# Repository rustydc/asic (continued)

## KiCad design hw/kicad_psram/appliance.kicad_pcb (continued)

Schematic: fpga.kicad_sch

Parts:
J_BMC_NET: BMC Ethernet; RJ45_MAGJACK
J_HOST: SlimSAS 8i host cable; SLIMSAS_8I
J_SFP: SFP+ cage; SFP_CAGE
U_BMC: BMC SoC; BGA_BMC_21x21
U_CLK: Si5345; QFN64_9x9
U_FPGA: XCAU15P-2FFVB676E; FFVB676_26x26_P1.0

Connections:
BMC_ETH0_N: J_BMC_NET.2, U_BMC.2
BMC_ETH0_P: J_BMC_NET.1, U_BMC.1
BMC_ETH1_N: J_BMC_NET.4, U_BMC.4
BMC_ETH1_P: J_BMC_NET.3, U_BMC.3
BMC_ETH2_N: J_BMC_NET.6, U_BMC.6
BMC_ETH2_P: J_BMC_NET.5, U_BMC.5
BMC_ETH3_N: J_BMC_NET.8, U_BMC.8
BMC_ETH3_P: J_BMC_NET.7, U_BMC.7
DDR4_ADDR_CMD0: U_FPGA.L24; also elsewhere on the board
DDR4_ADDR_CMD1: U_FPGA.M24; also elsewhere on the board
DDR4_ADDR_CMD2: U_FPGA.N24; also elsewhere on the board
DDR4_ADDR_CMD3: U_FPGA.P24; also elsewhere on the board
DDR4_ADDR_CMD4: U_FPGA.R24; also elsewhere on the board
DDR4_ADDR_CMD5: U_FPGA.T24; also elsewhere on the board
DDR4_ADDR_CMD6: U_FPGA.U24; also elsewhere on the board
DDR4_ADDR_CMD7: U_FPGA.V24; also elsewhere on the board
DDR4_ADDR_CMD8: U_FPGA.W24; also elsewhere on the board
DDR4_ADDR_CMD9: U_FPGA.Y24; also elsewhere on the board
DDR4_ADDR_CMD10: U_FPGA.AA24; also elsewhere on the board
DDR4_ADDR_CMD11: U_FPGA.AB24; also elsewhere on the board
DDR4_ADDR_CMD12: U_FPGA.C25; also elsewhere on the board
DDR4_ADDR_CMD13: U_FPGA.D25; also elsewhere on the board
DDR4_ADDR_CMD14: U_FPGA.E25; also elsewhere on the board
DDR4_ADDR_CMD15: U_FPGA.F25; also elsewhere on the board
DDR4_ADDR_CMD16: U_FPGA.G25; also elsewhere on the board
DDR4_ADDR_CMD17: U_FPGA.H25; also elsewhere on the board
DDR4_ADDR_CMD18: U_FPGA.J25; also elsewhere on the board
DDR4_ADDR_CMD19: U_FPGA.K25; also elsewhere on the board
DDR4_ADDR_CMD20: U_FPGA.L25; also elsewhere on the board
DDR4_ADDR_CMD21: U_FPGA.M25; also elsewhere on the board
DDR4_ADDR_CMD22: U_FPGA.N25; also elsewhere on the board
DDR4_ADDR_CMD23: U_FPGA.P25; also elsewhere on the board
DDR4_ADDR_CMD24: U_FPGA.R25; also elsewhere on the board
DDR4_ADDR_CMD25: U_FPGA.T25; also elsewhere on the board
DDR4_ADDR_CMD26: U_FPGA.U25; also elsewhere on the board
DDR4_ADDR_CMD27: U_FPGA.V25; also elsewhere on the board
DDR4_CK_N: U_FPGA.Y25; also elsewhere on the board
DDR4_CK_P: U_FPGA.W25; also elsewhere on the board
DDR4_CTRL0: U_FPGA.AA25; also elsewhere on the board
DDR4_CTRL1: U_FPGA.AB25; also elsewhere on the board
DDR4_CTRL2: U_FPGA.C26; also elsewhere on the board
DDR4_CTRL3: U_FPGA.D26; also elsewhere on the board
DDR4_CTRL4: U_FPGA.E26; also elsewhere on the board
DDR4_CTRL5: U_FPGA.F26; also elsewhere on the board
DDR4_DM0: U_FPGA.C24; also elsewhere on the board
DDR4_DM1: U_FPGA.D24; also elsewhere on the board
DDR4_DM2: U_FPGA.E24; also elsewhere on the board
DDR4_DM3: U_FPGA.F24; also elsewhere on the board
DDR4_DM4: U_FPGA.G24; also elsewhere on the board
DDR4_DM5: U_FPGA.H24; also elsewhere on the board
DDR4_DM6: U_FPGA.J24; also elsewhere on the board
DDR4_DM7: U_FPGA.K24; also elsewhere on the board
DDR4_DQ0: U_FPGA.C20; also elsewhere on the board
DDR4_DQ1: U_FPGA.D20; also elsewhere on the board
DDR4_DQ2: U_FPGA.E20; also elsewhere on the board
DDR4_DQ3: U_FPGA.F20; also elsewhere on the board
DDR4_DQ4: U_FPGA.G20; also elsewhere on the board
DDR4_DQ5: U_FPGA.H20; also elsewhere on the board
DDR4_DQ6: U_FPGA.J20; also elsewhere on the board
DDR4_DQ7: U_FPGA.K20; also elsewhere on the board
DDR4_DQ8: U_FPGA.L20; also elsewhere on the board
DDR4_DQ9: U_FPGA.M20; also elsewhere on the board
DDR4_DQ10: U_FPGA.N20; also elsewhere on the board
DDR4_DQ11: U_FPGA.P20; also elsewhere on the board
DDR4_DQ12: U_FPGA.R20; also elsewhere on the board
DDR4_DQ13: U_FPGA.T20; also elsewhere on the board
DDR4_DQ14: U_FPGA.U20; also elsewhere on the board
DDR4_DQ15: U_FPGA.V20; also elsewhere on the board
DDR4_DQ16: U_FPGA.W20; also elsewhere on the board
DDR4_DQ17: U_FPGA.Y20; also elsewhere on the board
DDR4_DQ18: U_FPGA.AA20; also elsewhere on the board
DDR4_DQ19: U_FPGA.AB20; also elsewhere on the board
DDR4_DQ20: U_FPGA.C21; also elsewhere on the board
DDR4_DQ21: U_FPGA.D21; also elsewhere on the board
DDR4_DQ22: U_FPGA.E21; also elsewhere on the board
DDR4_DQ23: U_FPGA.F21; also elsewhere on the board
DDR4_DQ24: U_FPGA.G21; also elsewhere on the board
DDR4_DQ25: U_FPGA.H21; also elsewhere on the board
DDR4_DQ26: U_FPGA.J21; also elsewhere on the board
DDR4_DQ27: U_FPGA.K21; also elsewhere on the board
DDR4_DQ28: U_FPGA.L21; also elsewhere on the board
DDR4_DQ29: U_FPGA.M21; also elsewhere on the board
DDR4_DQ30: U_FPGA.N21; also elsewhere on the board
DDR4_DQ31: U_FPGA.P21; also elsewhere on the board
DDR4_DQ32: U_FPGA.R21; also elsewhere on the board
DDR4_DQ33: U_FPGA.T21; also elsewhere on the board
DDR4_DQ34: U_FPGA.U21; also elsewhere on the board
DDR4_DQ35: U_FPGA.V21; also elsewhere on the board
DDR4_DQ36: U_FPGA.W21; also elsewhere on the board
DDR4_DQ37: U_FPGA.Y21; also elsewhere on the board
DDR4_DQ38: U_FPGA.AA21; also elsewhere on the board
DDR4_DQ39: U_FPGA.AB21; also elsewhere on the board
DDR4_DQ40: U_FPGA.C22; also elsewhere on the board
DDR4_DQ41: U_FPGA.D22; also elsewhere on the board
DDR4_DQ42: U_FPGA.E22; also elsewhere on the board
DDR4_DQ43: U_FPGA.F22; also elsewhere on the board
DDR4_DQ44: U_FPGA.G22; also elsewhere on the board
DDR4_DQ45: U_FPGA.H22; also elsewhere on the board
DDR4_DQ46: U_FPGA.J22; also elsewhere on the board
DDR4_DQ47: U_FPGA.K22; also elsewhere on the board
DDR4_DQ48: U_FPGA.L22; also elsewhere on the board
DDR4_DQ49: U_FPGA.M22; also elsewhere on the board
DDR4_DQ50: U_FPGA.N22; also elsewhere on the board
DDR4_DQ51: U_FPGA.P22; also elsewhere on the board
DDR4_DQ52: U_FPGA.R22; also elsewhere on the board
DDR4_DQ53: U_FPGA.T22; also elsewhere on the board
DDR4_DQ54: U_FPGA.U22; also elsewhere on the board
DDR4_DQ55: U_FPGA.V22; also elsewhere on the board
DDR4_DQ56: U_FPGA.W22; also elsewhere on the board
DDR4_DQ57: U_FPGA.Y22; also elsewhere on the board
DDR4_DQ58: U_FPGA.AA22; also elsewhere on the board
DDR4_DQ59: U_FPGA.AB22; also elsewhere on the board
DDR4_DQ60: U_FPGA.C23; also elsewhere on the board
DDR4_DQ61: U_FPGA.D23; also elsewhere on the board
DDR4_DQ62: U_FPGA.E23; also elsewhere on the board
DDR4_DQ63: U_FPGA.F23; also elsewhere on the board
DDR4_DQS0_N: U_FPGA.H23; also elsewhere on the board
DDR4_DQS0_P: U_FPGA.G23; also elsewhere on the board
DDR4_DQS1_N: U_FPGA.K23; also elsewhere on the board
DDR4_DQS1_P: U_FPGA.J23; also elsewhere on the board
DDR4_DQS2_N: U_FPGA.M23; also elsewhere on the board
DDR4_DQS2_P: U_FPGA.L23; also elsewhere on the board
DDR4_DQS3_N: U_FPGA.P23; also elsewhere on the board
DDR4_DQS3_P: U_FPGA.N23; also elsewhere on the board
DDR4_DQS4_N: U_FPGA.T23; also elsewhere on the board
DDR4_DQS4_P: U_FPGA.R23; also elsewhere on the board
DDR4_DQS5_N: U_FPGA.V23; also elsewhere on the board
DDR4_DQS5_P: U_FPGA.U23; also elsewhere on the board
DDR4_DQS6_N: U_FPGA.Y23; also elsewhere on the board
DDR4_DQS6_P: U_FPGA.W23; also elsewhere on the board
DDR4_DQS7_N: U_FPGA.AB23; also elsewhere on the board
DDR4_DQS7_P: U_FPGA.AA23; also elsewhere on the board
FAN_0_PWM: U_BMC.9; also elsewhere on the board
FAN_0_TACH: U_BMC.10; also elsewhere on the board
FAN_1_PWM: U_BMC.11; also elsewhere on the board
FAN_1_TACH: U_BMC.12; also elsewhere on the board
FAN_2_PWM: U_BMC.13; also elsewhere on the board
FAN_2_TACH: U_BMC.14; also elsewhere on the board
FAN_3_PWM: U_BMC.15; also elsewhere on the board
FAN_3_TACH: U_BMC.16; also elsewhere on the board
FAN_4_PWM: U_BMC.17; also elsewhere on the board
FAN_4_TACH: U_BMC.18; also elsewhere on the board
FAN_5_PWM: U_BMC.19; also elsewhere on the board
FAN_5_TACH: U_BMC.20; also elsewhere on the board
GND: J_BMC_NET.10, J_BMC_NET.11, J_BMC_NET.12, J_HOST.37, J_HOST.38, J_HOST.39, J_HOST.40, J_HOST.41, J_HOST.42, J_HOST.43, J_HOST.44, J_HOST.45, J_HOST.46, J_HOST.47, J_HOST.48, J_HOST.49, J_HOST.50, J_HOST.51, J_HOST.52, J_HOST.53, J_HOST.54, J_SFP.13, J_SFP.14, J_SFP.15, J_SFP.16, U_BMC.28, U_BMC.29, U_CLK.2, U_FPGA.A1, U_FPGA.A3, U_FPGA.A5, U_FPGA.A7, U_FPGA.A9, U_FPGA.A17, U_FPGA.A19, U_FPGA.A21, U_FPGA.A23, U_FPGA.A25, U_FPGA.AA1, U_FPGA.AA3, U_FPGA.AA5, U_FPGA.AA7, U_FPGA.AA9, U_FPGA.AA11, U_FPGA.AA13, U_FPGA.AA15, U_FPGA.AA17, U_FPGA.AA19, U_FPGA.AB2, U_FPGA.AB4, U_FPGA.AB6, U_FPGA.AB8, U_FPGA.AB10, U_FPGA.AB12, U_FPGA.AB14, U_FPGA.AB16, U_FPGA.AB18, U_FPGA.AB26, U_FPGA.AC25, U_FPGA.AD26, U_FPGA.AE23, U_FPGA.AE25, U_FPGA.B2, U_FPGA.B4, U_FPGA.B6, U_FPGA.B8, U_FPGA.B10, U_FPGA.B18, U_FPGA.B20, U_FPGA.B22, U_FPGA.B24, U_FPGA.B26, U_FPGA.C1, U_FPGA.C3, U_FPGA.C5, U_FPGA.C7, U_FPGA.C9, U_FPGA.C11, U_FPGA.C13, U_FPGA.C15, U_FPGA.C17, U_FPGA.C19, U_FPGA.D2, U_FPGA.D4, U_FPGA.D6, U_FPGA.D8, U_FPGA.D10, U_FPGA.D12, U_FPGA.D14, U_FPGA.D16, U_FPGA.D18, U_FPGA.E1, U_FPGA.E3, U_FPGA.E5, U_FPGA.E7, U_FPGA.E9, U_FPGA.E11, U_FPGA.E13, U_FPGA.E15, U_FPGA.E17, U_FPGA.E19, U_FPGA.F2, U_FPGA.F4, U_FPGA.F6, U_FPGA.F8, U_FPGA.F10, U_FPGA.F12, U_FPGA.F14, U_FPGA.F16, U_FPGA.F18, U_FPGA.G1, U_FPGA.G3, U_FPGA.G5, U_FPGA.G7, U_FPGA.G9, U_FPGA.G11, U_FPGA.G13, U_FPGA.G15, U_FPGA.G17, U_FPGA.G19, U_FPGA.H2, U_FPGA.H4, U_FPGA.H6, U_FPGA.H8, U_FPGA.H10, U_FPGA.H12, U_FPGA.H14, U_FPGA.H16, U_FPGA.H18, U_FPGA.H26, U_FPGA.J1, U_FPGA.J3, U_FPGA.J5, U_FPGA.J7, U_FPGA.J9, U_FPGA.J11, U_FPGA.J13, U_FPGA.J15, U_FPGA.J17, U_FPGA.J19, U_FPGA.K2, U_FPGA.K4, U_FPGA.K6, U_FPGA.K8, U_FPGA.K10, U_FPGA.K12, U_FPGA.K14, U_FPGA.K16, U_FPGA.K18, U_FPGA.K26, U_FPGA.L1, U_FPGA.L3, U_FPGA.L5, U_FPGA.L7, U_FPGA.L9, U_FPGA.L11, U_FPGA.L13, U_FPGA.L15, U_FPGA.L17, U_FPGA.L19, U_FPGA.M2, U_FPGA.M4, U_FPGA.M6, U_FPGA.M8, U_FPGA.M10, U_FPGA.M12, U_FPGA.M14, U_FPGA.M16, U_FPGA.M18, U_FPGA.M26, U_FPGA.N1, U_FPGA.N3, U_FPGA.N5, U_FPGA.N7, U_FPGA.N9, U_FPGA.N11, U_FPGA.N13, U_FPGA.N15, U_FPGA.N17, U_FPGA.N19, U_FPGA.P2, U_FPGA.P4, U_FPGA.P6, U_FPGA.P8, U_FPGA.P10, U_FPGA.P12, U_FPGA.P14, U_FPGA.P16, U_FPGA.P18, U_FPGA.P26, U_FPGA.R1, U_FPGA.R3, U_FPGA.R5, U_FPGA.R7, U_FPGA.R9, U_FPGA.R11, U_FPGA.R13, U_FPGA.R15, U_FPGA.R17, U_FPGA.R19, U_FPGA.T2, U_FPGA.T4, U_FPGA.T6, U_FPGA.T8, U_FPGA.T10, U_FPGA.T12, U_FPGA.T14, U_FPGA.T16, U_FPGA.T18, U_FPGA.T26, U_FPGA.U1, U_FPGA.U3, U_FPGA.U5, U_FPGA.U7, U_FPGA.U9, U_FPGA.U11, U_FPGA.U13, U_FPGA.U15, U_FPGA.U17, U_FPGA.U19, U_FPGA.V2, U_FPGA.V4, U_FPGA.V6, U_FPGA.V8, U_FPGA.V10, U_FPGA.V12, U_FPGA.V14, U_FPGA.V16, U_FPGA.V18, U_FPGA.V26, U_FPGA.W1, U_FPGA.W3, U_FPGA.W5, U_FPGA.W7, U_FPGA.W9, U_FPGA.W11, U_FPGA.W13, U_FPGA.W15, U_FPGA.W17, U_FPGA.W19, U_FPGA.Y2, U_FPGA.Y4, U_FPGA.Y6, U_FPGA.Y8, U_FPGA.Y10, U_FPGA.Y12, U_FPGA.Y14, U_FPGA.Y16, U_FPGA.Y18, U_FPGA.Y26; also elsewhere on the board
JTAG_TCK: U_FPGA.AC24; also elsewhere on the board
JTAG_TDI_FPGA: U_FPGA.AD2
JTAG_TDO_FPGA: U_FPGA.AD3; also elsewhere on the board
JTAG_TMS: U_FPGA.AD1; also elsewhere on the board
JTAG_TRST: U_FPGA.AD4; also elsewhere on the board
LINK0_CLOCK: U_FPGA.B12; also elsewhere on the board
LINK0_DATA0: U_FPGA.B16; also elsewhere on the board
LINK0_DATA1: U_FPGA.A16; also elsewhere on the board
LINK0_DATA2: U_FPGA.B15; also elsewhere on the board
LINK0_DATA3: U_FPGA.A15; also elsewhere on the board
LINK0_DATA4: U_FPGA.B14; also elsewhere on the board
LINK0_DATA5: U_FPGA.A14; also elsewhere on the board
LINK0_DATA6: U_FPGA.B13; also elsewhere on the board
LINK0_DATA7: U_FPGA.A13; also elsewhere on the board
LINK0_READY_BACK: U_FPGA.B11; also elsewhere on the board
LINK0_SOF: U_FPGA.A11; also elsewhere on the board
LINK0_VALID: U_FPGA.A12; also elsewhere on the board
LINK10_CLOCK: U_FPGA.AE12; also elsewhere on the board
LINK10_DATA0: U_FPGA.AE16; also elsewhere on the board
LINK10_DATA1: U_FPGA.AF16; also elsewhere on the board
LINK10_DATA2: U_FPGA.AE15; also elsewhere on the board
LINK10_DATA3: U_FPGA.AF15; also elsewhere on the board
LINK10_DATA4: U_FPGA.AE14; also elsewhere on the board
LINK10_DATA5: U_FPGA.AF14; also elsewhere on the board
LINK10_DATA6: U_FPGA.AE13; also elsewhere on the board
LINK10_DATA7: U_FPGA.AF13; also elsewhere on the board
LINK10_READY_BACK: U_FPGA.AE11; also elsewhere on the board
LINK10_SOF: U_FPGA.AF11; also elsewhere on the board
LINK10_VALID: U_FPGA.AF12; also elsewhere on the board
MGMT_CS_A0: U_FPGA.AC4; also elsewhere on the board
MGMT_CS_A1: U_FPGA.AC6; also elsewhere on the board
MGMT_CS_A2: U_FPGA.AC8; also elsewhere on the board
MGMT_CS_A3: U_FPGA.AC10; also elsewhere on the board
MGMT_CS_A4: U_FPGA.AC12; also elsewhere on the board
MGMT_CS_A5: U_FPGA.AC14; also elsewhere on the board
MGMT_CS_A6: U_FPGA.AC16; also elsewhere on the board
MGMT_CS_A7: U_FPGA.AC18; also elsewhere on the board
MGMT_CS_H0: U_FPGA.AC20; also elsewhere on the board
MGMT_CS_H1: U_FPGA.AC22; also elsewhere on the board
MGMT_IRQ_A0: U_FPGA.AC5; also elsewhere on the board
MGMT_IRQ_A1: U_FPGA.AC7; also elsewhere on the board
MGMT_IRQ_A2: U_FPGA.AC9; also elsewhere on the board
MGMT_IRQ_A3: U_FPGA.AC11; also elsewhere on the board
MGMT_IRQ_A4: U_FPGA.AC13; also elsewhere on the board
MGMT_IRQ_A5: U_FPGA.AC15; also elsewhere on the board
MGMT_IRQ_A6: U_FPGA.AC17; also elsewhere on the board
MGMT_IRQ_A7: U_FPGA.AC19; also elsewhere on the board
MGMT_IRQ_H0: U_FPGA.AC21; also elsewhere on the board
MGMT_IRQ_H1: U_FPGA.AC23; also elsewhere on the board
MGMT_MISO: U_FPGA.AC3; also elsewhere on the board
MGMT_MOSI: U_FPGA.AC2; also elsewhere on the board
MGMT_SCLK: U_FPGA.AC1; also elsewhere on the board
MGTAVCC: U_FPGA.AB5, U_FPGA.D5, U_FPGA.G18, U_FPGA.N2, U_FPGA.T9; also elsewhere on the board
MGTAVTT: U_FPGA.AB11, U_FPGA.D11, U_FPGA.K1, U_FPGA.N8, U_FPGA.T15; also elsewhere on the board
PCIE_PERST: J_HOST.35, U_FPGA.AE21
PCIE_REFCLK_N: J_HOST.34, U_FPGA.AE20
PCIE_REFCLK_P: J_HOST.33, U_FPGA.AE19
PCIE_RX0_N: J_HOST.18, U_FPGA.AF24
PCIE_RX0_P: J_HOST.17, U_FPGA.AF23
PCIE_RX1_N: J_HOST.20, U_FPGA.AF26
PCIE_RX1_P: J_HOST.19, U_FPGA.AF25
PCIE_RX2_N: J_HOST.22, U_FPGA.AE2
PCIE_RX2_P: J_HOST.21, U_FPGA.AE1
PCIE_RX3_N: J_HOST.24, U_FPGA.AE4
PCIE_RX3_P: J_HOST.23, U_FPGA.AE3
PCIE_RX4_N: J_HOST.26, U_FPGA.AE6
PCIE_RX4_P: J_HOST.25, U_FPGA.AE5
PCIE_RX5_N: J_HOST.28, U_FPGA.AE8
PCIE_RX5_P: J_HOST.27, U_FPGA.AE7
PCIE_RX6_N: J_HOST.30, U_FPGA.AE10
PCIE_RX6_P: J_HOST.29, U_FPGA.AE9
PCIE_RX7_N: J_HOST.32, U_FPGA.AE18
PCIE_RX7_P: J_HOST.31, U_FPGA.AE17
PCIE_TX0_N: J_HOST.2, U_FPGA.AF2
PCIE_TX0_P: J_HOST.1, U_FPGA.AF1
PCIE_TX1_N: J_HOST.4, U_FPGA.AF4
PCIE_TX1_P: J_HOST.3, U_FPGA.AF3
PCIE_TX2_N: J_HOST.6, U_FPGA.AF6
PCIE_TX2_P: J_HOST.5, U_FPGA.AF5
PCIE_TX3_N: J_HOST.8, U_FPGA.AF8
PCIE_TX3_P: J_HOST.7, U_FPGA.AF7
PCIE_TX4_N: J_HOST.10, U_FPGA.AF10
PCIE_TX4_P: J_HOST.9, U_FPGA.AF9
PCIE_TX5_N: J_HOST.12, U_FPGA.AF18
PCIE_TX5_P: J_HOST.11, U_FPGA.AF17
PCIE_TX6_N: J_HOST.14, U_FPGA.AF20
PCIE_TX6_P: J_HOST.13, U_FPGA.AF19
PCIE_TX7_N: J_HOST.16, U_FPGA.AF22
PCIE_TX7_P: J_HOST.15, U_FPGA.AF21
PCIE_WAKE: J_HOST.36, U_FPGA.AE22
PMB_SCL: U_BMC.23; also elsewhere on the board
PMB_SDA: U_BMC.24; also elsewhere on the board
PSU_ON: U_BMC.25; also elsewhere on the board
QSPI0: U_FPGA.AD17
QSPI1: U_FPGA.AD18
QSPI2: U_FPGA.AD19
QSPI3: U_FPGA.AD20
QSPI4: U_FPGA.AD21
QSPI5: U_FPGA.AD22
REFCLK_A0_N: U_CLK.6; also elsewhere on the board
REFCLK_A0_P: U_CLK.5; also elsewhere on the board
REFCLK_A1_N: U_CLK.8; also elsewhere on the board
REFCLK_A1_P: U_CLK.7; also elsewhere on the board
REFCLK_A2_N: U_CLK.10; also elsewhere on the board
REFCLK_A2_P: U_CLK.9; also elsewhere on the board
REFCLK_A3_N: U_CLK.12; also elsewhere on the board
REFCLK_A3_P: U_CLK.11; also elsewhere on the board
REFCLK_A4_N: U_CLK.14; also elsewhere on the board
REFCLK_A4_P: U_CLK.13; also elsewhere on the board
REFCLK_A5_N: U_CLK.16; also elsewhere on the board
REFCLK_A5_P: U_CLK.15; also elsewhere on the board
REFCLK_A6_N: U_CLK.18; also elsewhere on the board
REFCLK_A6_P: U_CLK.17; also elsewhere on the board
REFCLK_A7_N: U_CLK.20; also elsewhere on the board
REFCLK_A7_P: U_CLK.19; also elsewhere on the board
REFCLK_FPGA_N: U_CLK.4, U_FPGA.AD6
REFCLK_FPGA_P: U_CLK.3, U_FPGA.AD5
REFCLK_H0_N: U_CLK.22; also elsewhere on the board
REFCLK_H0_P: U_CLK.21; also elsewhere on the board
REFCLK_H1_N: U_CLK.24; also elsewhere on the board
REFCLK_H1_P: U_CLK.23; also elsewhere on the board
SFP_CTRL0: J_SFP.7, U_FPGA.AD13
SFP_CTRL1: J_SFP.8, U_FPGA.AD14
SFP_CTRL2: J_SFP.9, U_FPGA.AD15
SFP_CTRL3: J_SFP.10, U_FPGA.AD16
SFP_I2C0: J_SFP.5, U_FPGA.AD11
SFP_I2C1: J_SFP.6, U_FPGA.AD12
SFP_RX_N: J_SFP.4, U_FPGA.AD10
SFP_RX_P: J_SFP.3, U_FPGA.AD9
SFP_TX_N: J_SFP.2, U_FPGA.AD8
SFP_TX_P: J_SFP.1, U_FPGA.AD7
UART_RX: U_BMC.22, U_FPGA.AD24
UART_TX: U_BMC.21, U_FPGA.AD23
VCCAUX_1V8: U_FPGA.A4, U_FPGA.AB17, U_FPGA.D17, U_FPGA.K7, U_FPGA.N14, U_FPGA.W4; also elsewhere on the board
VCCINT_0V85: U_FPGA.A2, U_FPGA.A6, U_FPGA.A8, U_FPGA.A18, U_FPGA.A20, U_FPGA.A24, U_FPGA.A26, U_FPGA.AA2, U_FPGA.AA4, U_FPGA.AA6, U_FPGA.AA8, U_FPGA.AA10, U_FPGA.AA12, U_FPGA.AA14, U_FPGA.AA16, U_FPGA.AA18, U_FPGA.AA26, U_FPGA.AB1, U_FPGA.AB3, U_FPGA.AB7, U_FPGA.AB9, U_FPGA.AB13, U_FPGA.AB15, U_FPGA.AB19, U_FPGA.AC26, U_FPGA.AD25, U_FPGA.AE26, U_FPGA.B1, U_FPGA.B3, U_FPGA.B5, U_FPGA.B7, U_FPGA.B9, U_FPGA.B17, U_FPGA.B19, U_FPGA.B21, U_FPGA.B23, U_FPGA.B25, U_FPGA.C2, U_FPGA.C4, U_FPGA.C6, U_FPGA.C8, U_FPGA.C10, U_FPGA.C12, U_FPGA.C14, U_FPGA.C16, U_FPGA.C18, U_FPGA.D1, U_FPGA.D3, U_FPGA.D7, U_FPGA.D9, U_FPGA.D13, U_FPGA.D15, U_FPGA.D19, U_FPGA.E2, U_FPGA.E4, U_FPGA.E6, U_FPGA.E8, U_FPGA.E10, U_FPGA.E12, U_FPGA.E14, U_FPGA.E16, U_FPGA.E18, U_FPGA.F1, U_FPGA.F3, U_FPGA.F5, U_FPGA.F7, U_FPGA.F9, U_FPGA.F11, U_FPGA.F13, U_FPGA.F15, U_FPGA.F17, U_FPGA.F19, U_FPGA.G2, U_FPGA.G4, U_FPGA.G8, U_FPGA.G10, U_FPGA.G14, U_FPGA.G16, U_FPGA.G26, U_FPGA.H1, U_FPGA.H3, U_FPGA.H5, U_FPGA.H7, U_FPGA.H9, U_FPGA.H11, U_FPGA.H13, U_FPGA.H15, U_FPGA.H17, U_FPGA.H19, U_FPGA.J2, U_FPGA.J4, U_FPGA.J6, U_FPGA.J8, U_FPGA.J10, U_FPGA.J12, U_FPGA.J14, U_FPGA.J16, U_FPGA.J18, U_FPGA.J26, U_FPGA.K3, U_FPGA.K5, U_FPGA.K9, U_FPGA.K11, U_FPGA.K15, U_FPGA.K17, U_FPGA.L2, U_FPGA.L4, U_FPGA.L6, U_FPGA.L8, U_FPGA.L10, U_FPGA.L12, U_FPGA.L14, U_FPGA.L16, U_FPGA.L18, U_FPGA.L26, U_FPGA.M1, U_FPGA.M3, U_FPGA.M5, U_FPGA.M7, U_FPGA.M9, U_FPGA.M11, U_FPGA.M13, U_FPGA.M15, U_FPGA.M17, U_FPGA.M19, U_FPGA.N4, U_FPGA.N6, U_FPGA.N10, U_FPGA.N12, U_FPGA.N16, U_FPGA.N18, U_FPGA.P1, U_FPGA.P3, U_FPGA.P5, U_FPGA.P7, U_FPGA.P9, U_FPGA.P11, U_FPGA.P13, U_FPGA.P15, U_FPGA.P17, U_FPGA.P19, U_FPGA.R2, U_FPGA.R4, U_FPGA.R6, U_FPGA.R8, U_FPGA.R10, U_FPGA.R12, U_FPGA.R14, U_FPGA.R16, U_FPGA.R18, U_FPGA.R26, U_FPGA.T1, U_FPGA.T5, U_FPGA.T7, U_FPGA.T11, U_FPGA.T13, U_FPGA.T17, U_FPGA.T19, U_FPGA.U2, U_FPGA.U4, U_FPGA.U6, U_FPGA.U8, U_FPGA.U10, U_FPGA.U12, U_FPGA.U14, U_FPGA.U16, U_FPGA.U18, U_FPGA.U26, U_FPGA.V1, U_FPGA.V3, U_FPGA.V5, U_FPGA.V7, U_FPGA.V9, U_FPGA.V11, U_FPGA.V13, U_FPGA.V15, U_FPGA.V17, U_FPGA.V19, U_FPGA.W2, U_FPGA.W6, U_FPGA.W8, U_FPGA.W12, U_FPGA.W14, U_FPGA.W18, U_FPGA.W26, U_FPGA.Y1, U_FPGA.Y3, U_FPGA.Y5, U_FPGA.Y7, U_FPGA.Y9, U_FPGA.Y11, U_FPGA.Y13, U_FPGA.Y15, U_FPGA.Y17, U_FPGA.Y19; also elsewhere on the board
VCCO_1V2: U_FPGA.A22, U_FPGA.G12, U_FPGA.K19, U_FPGA.T3, U_FPGA.W16; also elsewhere on the board
VCCO_1V8: U_FPGA.A10, U_FPGA.AE24, U_FPGA.G6, U_FPGA.K13, U_FPGA.N26, U_FPGA.W10; also elsewhere on the board
VDD_3V3: J_BMC_NET.9, J_SFP.11, J_SFP.12, U_BMC.26, U_BMC.27; also elsewhere on the board
VDD_IO_1V8: U_CLK.1; also elsewhere on the board

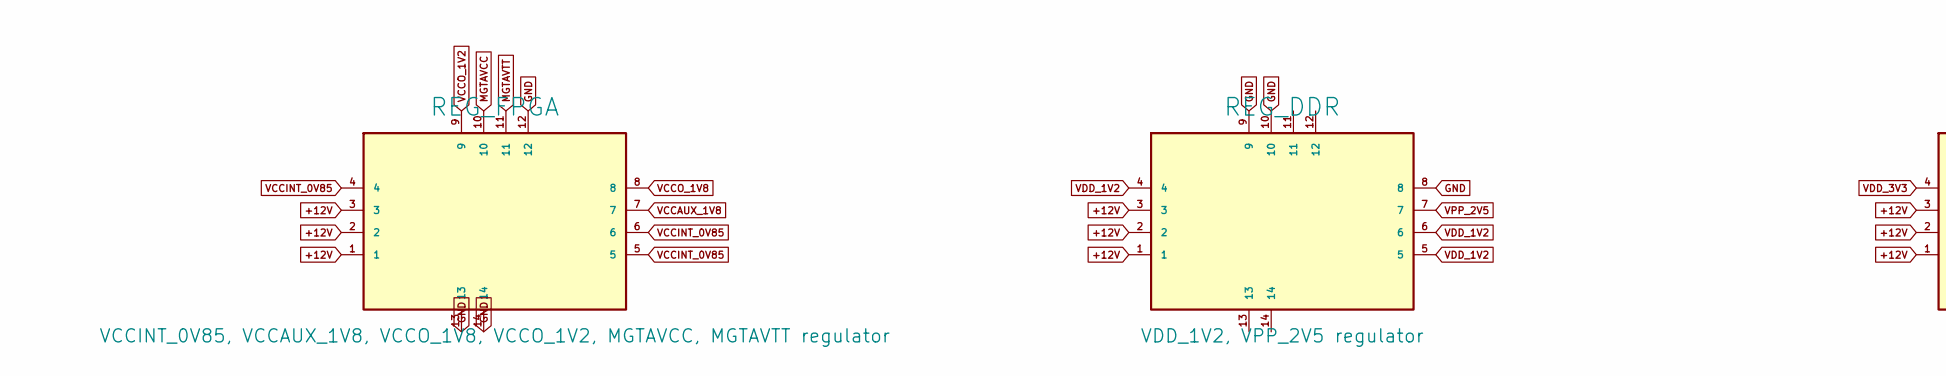
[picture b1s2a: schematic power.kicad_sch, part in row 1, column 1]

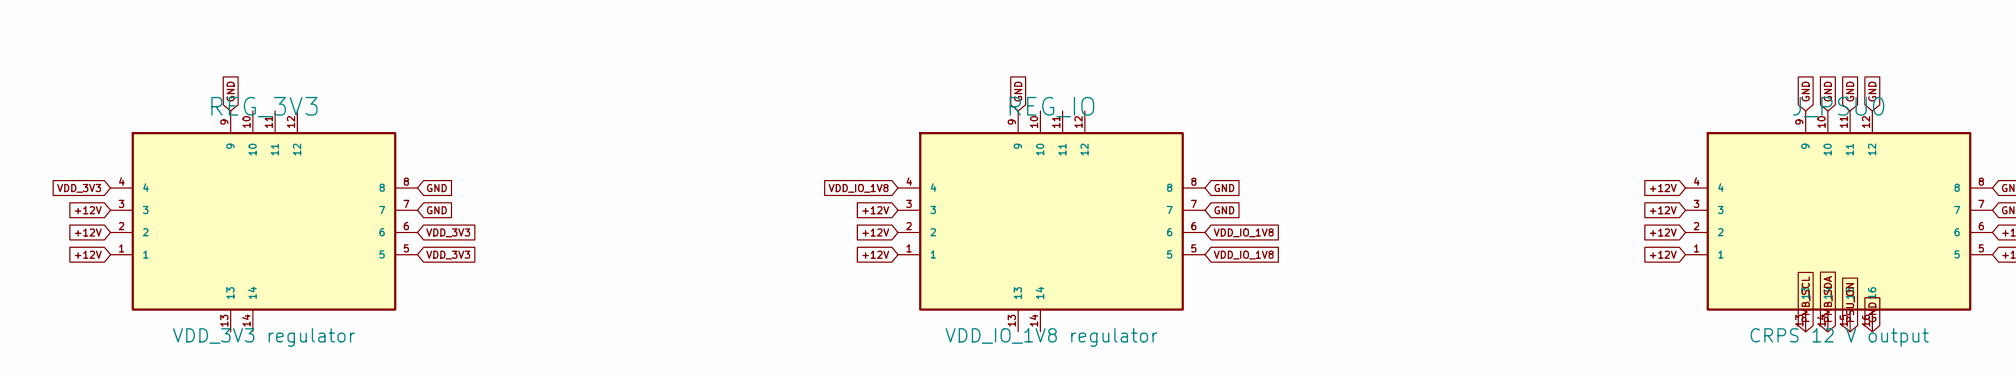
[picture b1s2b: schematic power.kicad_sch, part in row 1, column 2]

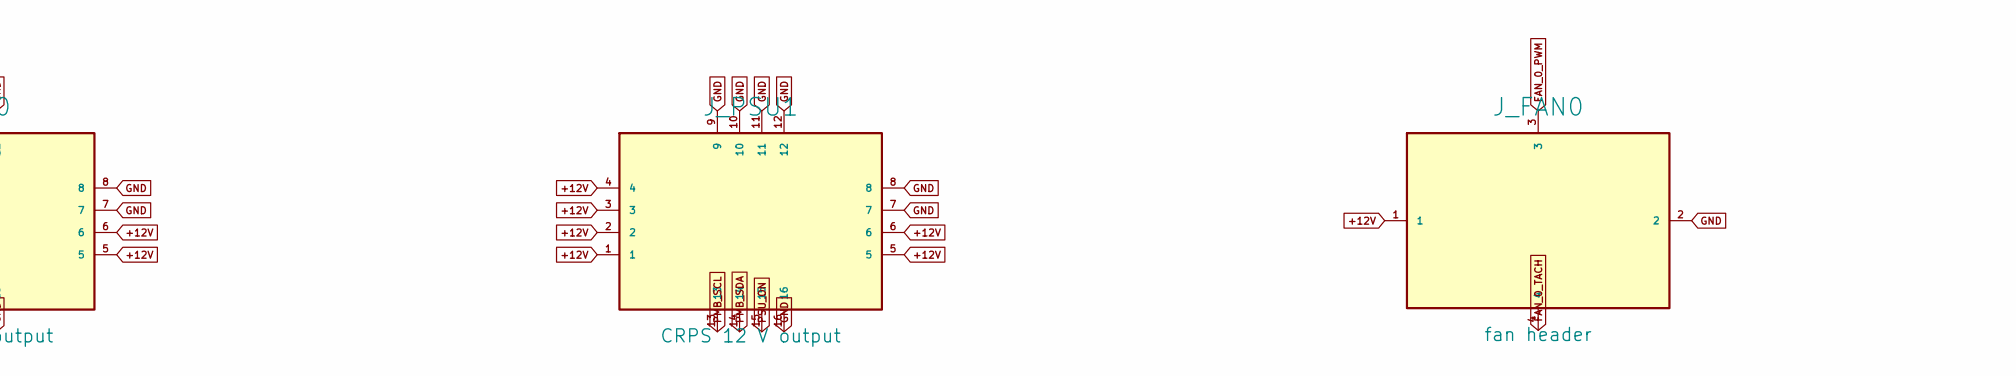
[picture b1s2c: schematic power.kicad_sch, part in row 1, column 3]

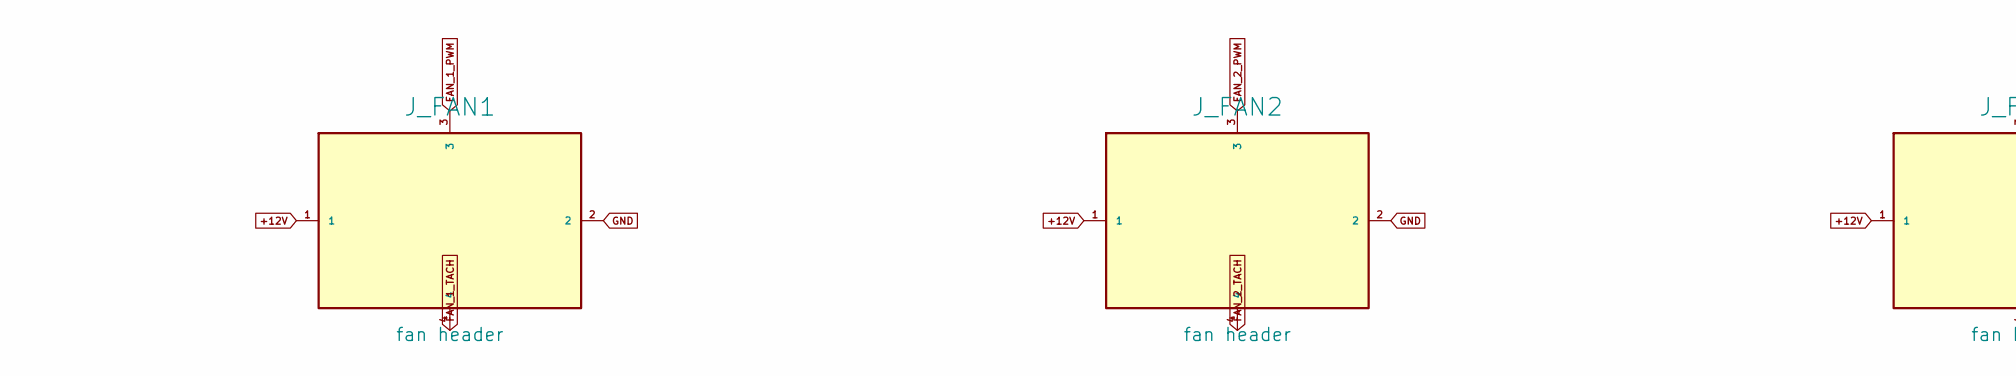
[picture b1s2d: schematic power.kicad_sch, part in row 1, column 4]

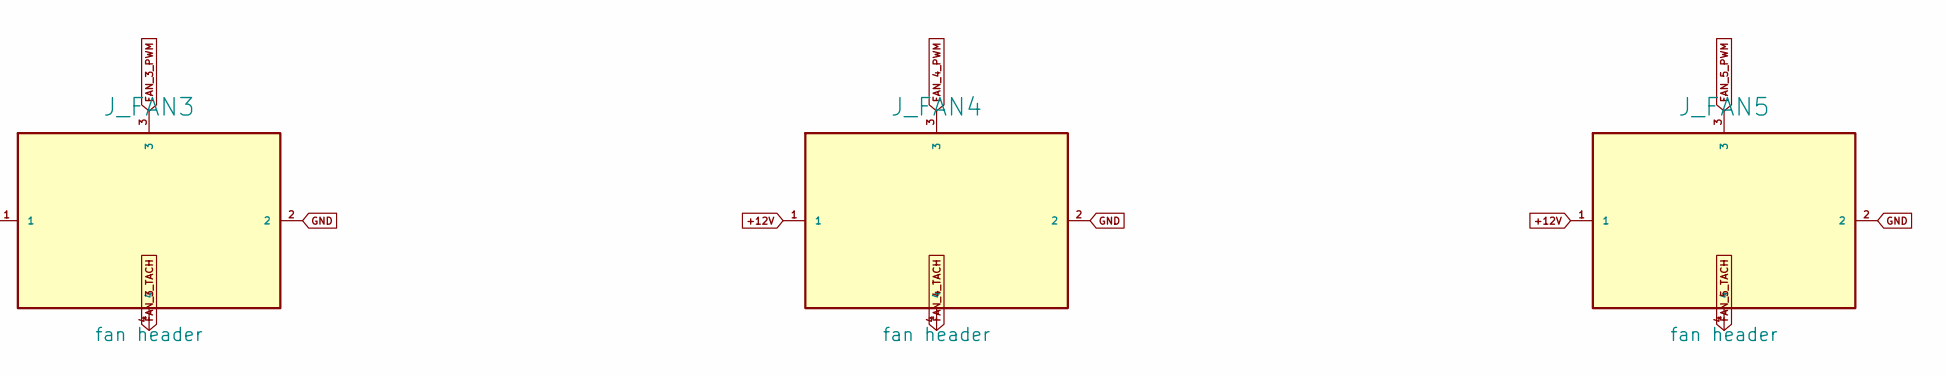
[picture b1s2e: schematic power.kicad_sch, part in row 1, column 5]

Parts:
J_FAN0, J_FAN1, J_FAN2, J_FAN3, J_FAN4, J_FAN5: fan header; FAN_4PIN
J_PSU0, J_PSU1: CRPS 12 V output; CRPS_BLADES
REG_3V3: VDD_3V3 regulator; REG_MODULE_20x6
REG_DDR: VDD_1V2, VPP_2V5 regulator; REG_MODULE_20x6
REG_FPGA: VCCINT_0V85, VCCAUX_1V8, VCCO_1V8, VCCO_1V2, MGTA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; REG_MODULE_20x6
REG_IO: VDD_IO_1V8 regulator; REG_MODULE_20x6

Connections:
+12V: J_FAN0.1, J_FAN1.1, J_FAN2.1, J_FAN3.1, J_FAN4.1, J_FAN5.1, J_PSU0.1, J_PSU0.2, J_PSU0.3, J_PSU0.4, J_PSU0.5, J_PSU0.6, J_PSU1.1, J_PSU1.2, J_PSU1.3, J_PSU1.4, J_PSU1.5, J_PSU1.6, REG_3V3.1, REG_3V3.2, REG_3V3.3, REG_DDR.1, REG_DDR.2, REG_DDR.3, REG_FPGA.1, REG_FPGA.2, REG_FPGA.3, REG_IO.1, REG_IO.2, REG_IO.3; also elsewhere on the board
FAN_0_PWM: J_FAN0.3; also elsewhere on the board
FAN_0_TACH: J_FAN0.4; also elsewhere on the board
FAN_1_PWM: J_FAN1.3; also elsewhere on the board
FAN_1_TACH: J_FAN1.4; also elsewhere on the board
FAN_2_PWM: J_FAN2.3; also elsewhere on the board
FAN_2_TACH: J_FAN2.4; also elsewhere on the board
FAN_3_PWM: J_FAN3.3; also elsewhere on the board
FAN_3_TACH: J_FAN3.4; also elsewhere on the board
FAN_4_PWM: J_FAN4.3; also elsewhere on the board
FAN_4_TACH: J_FAN4.4; also elsewhere on the board
FAN_5_PWM: J_FAN5.3; also elsewhere on the board
FAN_5_TACH: J_FAN5.4; also elsewhere on the board
GND: J_FAN0.2, J_FAN1.2, J_FAN2.2, J_FAN3.2, J_FAN4.2, J_FAN5.2, J_PSU0.7, J_PSU0.8, J_PSU0.9, J_PSU0.10, J_PSU0.11, J_PSU0.12, J_PSU0.16, J_PSU1.7, J_PSU1.8, J_PSU1.9, J_PSU1.10, J_PSU1.11, J_PSU1.12, J_PSU1.16, REG_3V3.7, REG_3V3.8, REG_3V3.9, REG_DDR.8, REG_DDR.9, REG_DDR.10, REG_FPGA.12, REG_FPGA.13, REG_FPGA.14, REG_IO.7, REG_IO.8, REG_IO.9; also elsewhere on the board
MGTAVCC: REG_FPGA.10; also elsewhere on the board
MGTAVTT: REG_FPGA.11; also elsewhere on the board
PMB_SCL: J_PSU0.13, J_PSU1.13; also elsewhere on the board
PMB_SDA: J_PSU0.14, J_PSU1.14; also elsewhere on the board
PSU_ON: J_PSU0.15, J_PSU1.15; also elsewhere on the board
VCCAUX_1V8: REG_FPGA.7; also elsewhere on the board
VCCINT_0V85: REG_FPGA.4, REG_FPGA.5, REG_FPGA.6; also elsewhere on the board
VCCO_1V2: REG_FPGA.9; also elsewhere on the board
VCCO_1V8: REG_FPGA.8; also elsewhere on the board
VDD_1V2: REG_DDR.4, REG_DDR.5, REG_DDR.6; also elsewhere on the board
VDD_3V3: REG_3V3.4, REG_3V3.5, REG_3V3.6; also elsewhere on the board
VDD_IO_1V8: REG_IO.4, REG_IO.5, REG_IO.6; also elsewhere on the board
VPP_2V5: REG_DDR.7; also elsewhere on the board

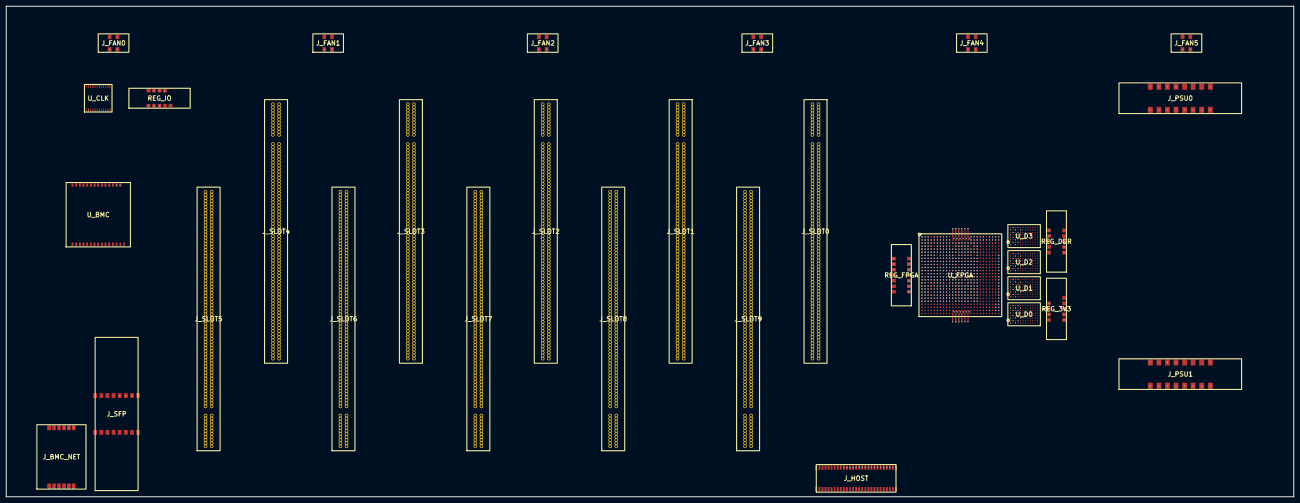
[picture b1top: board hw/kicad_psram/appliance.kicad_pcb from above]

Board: 6 copper layers, 420.0 x 160.0 mm, 32 parts (0 on the bottom side), 397 nets.
